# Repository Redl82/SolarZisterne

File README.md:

# SolarZisterne

Es handelt sich bei diesem Projekt um einen Füllstandsmesser für eine Außen-Zisterne.
Der Füllstandsmesser wir über einen ESP8266 mit dem Netzwerkverbunden und agiert als eigenständiger Web-Server.
Die Stromversorgung wird über Solarzellen gewährleistet.
Das Projekt besitz die folgenden Sensoren:
- Ultraschall Sensor für Füllstand
- Temperatur/Luftfeuchte/Luftdruck Sensor außen
- Temperatur/Luftdruck Sensor innen
- Spannung/Strom Sensor Produktion Solarzellen
- Spannung/Strom Sensor Verbrauch Elektronik

Die Lade Schaltung kann die follgenden Zustände annehmen:
            GPIO2   GPIO1   GPIO0
     Wert   STAT1   STAT2   PG      Status
     7      1       1       1       Input Power Not OK / Shutdown
     6      1       1       0       Input Power OK / No Battery Present
     4      1       0       0       Input Power OK / Charge Complete - Standby
     3      0       1       1       Input Power Not OK / Low Battery Output
     2      0       1       0       Input Power OK / Chargin Batter in Constant Current/Voltage or Preconding Mode
     0      0       0       0       Input Power OK / Temperature Fault / Temperatur Fault

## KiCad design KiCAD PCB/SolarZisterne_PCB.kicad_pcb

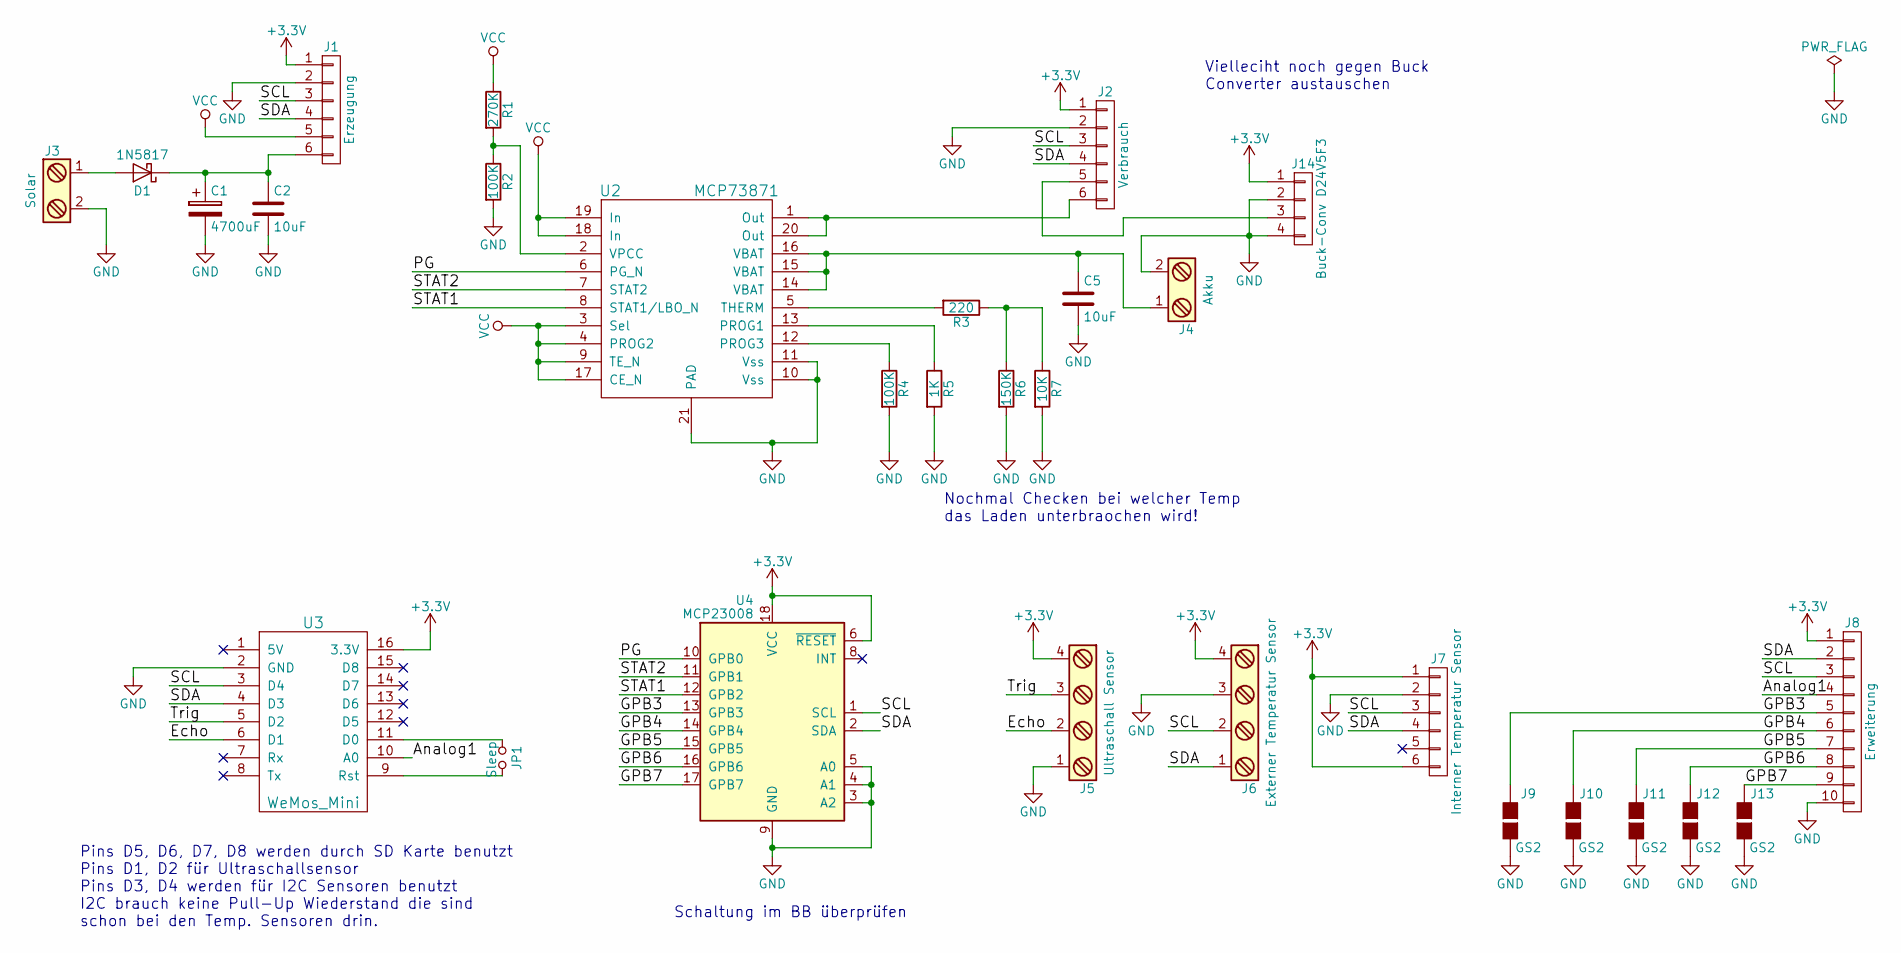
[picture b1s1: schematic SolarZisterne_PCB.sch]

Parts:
C1: 4700uF; CP_Radial_D16.0mm_P7.50mm
C2, C5: 10uF; C_Disc_D5.0mm_W2.5mm_P2.50mm
D1: 1N5817; D_DO-41_SOD81_P10.16mm_Horizontal
J1: Erzeugung; Pin_Header_Straight_1x06_Pitch2.54mm
J2: Verbrauch; Pin_Header_Straight_1x06_Pitch2.54mm
J3: Solar; TerminalBlock_Pheonix_PT-3.5mm_2pol
J4: Akku; TerminalBlock_Pheonix_PT-3.5mm_2pol
J5: Ultraschall Sensor; TerminalBlock_Pheonix_PT-3.5mm_4pol
J6: Externer Temperatur Sensor; TerminalBlock_Pheonix_PT-3.5mm_4pol
J7: Interner Temperatur Sensor; Pin_Header_Straight_1x06_Pitch2.54mm
J8: Erweiterung; Pin_Header_Straight_1x10_Pitch2.54mm
J9, J10, J11, J12, J13: GS2
J14: Buck-Conv D24V5F3; Pin_Header_Straight_1x04_Pitch2.54mm
JP1: Sleep; Pin_Header_Straight_1x02_Pitch2.54mm
R1: 270K; R_Axial_DIN0207_L6.3mm_D2.5mm_P10.16mm_Horizontal
R2, R4: 100K; R_Axial_DIN0207_L6.3mm_D2.5mm_P10.16mm_Horizontal
R3: 220; R_Axial_DIN0207_L6.3mm_D2.5mm_P10.16mm_Horizontal
R5: 1K; R_Axial_DIN0207_L6.3mm_D2.5mm_P10.16mm_Horizontal
R6: 150K; R_Axial_DIN0207_L6.3mm_D2.5mm_P10.16mm_Horizontal
R7: 10K; R_Axial_DIN0207_L6.3mm_D2.5mm_P10.16mm_Horizontal
U2: MCP73871; QFN-20-1EP_4x4mm_Pitch0.5mm
U3: WeMos_Mini; D1_mini_board
U4: MCP23008; DIP-18_W7.62mm_LongPads

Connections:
+3V3: J1.1, J2.1, J5.4, J6.4, J7.1, J7.6, J8.1, J14.1, U3.16 (3.3V), U4.6 (~RESET), U4.18 (VCC)
/Analog1: J8.4, U3.10 (A0)
/Echo: J5.2, U3.6 (D1)
/GPB3: J8.5, J9.1 (G1), U4.13 (GPB3)
/GPB4: J8.6, J10.1 (G1), U4.14 (GPB4)
/GPB5: J8.7, J11.1 (G1), U4.15 (GPB5)
/GPB6: J8.8, J12.1 (G1), U4.16 (GPB6)
/GPB7: J8.9, J13.1 (G1), U4.17 (GPB7)
/PG: U2.6 (PG_N), U4.10 (GPB0)
/SCL: J1.3, J2.3, J6.2, J7.3, J8.3, U3.3 (D4), U4.1 (SCL)
/SDA: J1.4, J2.4, J6.1, J7.4, J8.2, U3.4 (D3), U4.2 (SDA)
/STAT1: U2.8 (STAT1/LBO_N), U4.12 (GPB2)
/STAT2: U2.7 (STAT2), U4.11 (GPB1)
/Trig: J5.3, U3.5 (D2)
GND: C1.2, C2.2, C5.2, J1.2, J2.2, J3.2, J4.2, J5.1, J6.3, J7.2, J8.10, J9.2 (G2), J10.2 (G2), J11.2 (G2), J12.2 (G2), J13.2 (G2), J14.2, J14.4, R2.2, R4.2, R5.2, R6.2, R7.2, U2.10 (Vss), U2.11 (Vss), U2.21 (PAD), U3.2 (GND), U4.3 (A2), U4.4 (A1), U4.5 (A0), U4.9 (GND)
unnamed: C1.1, C2.1, D1.1 (K), J1.6
unnamed: C5.1, J4.1, U2.14 (VBAT), U2.15 (VBAT), U2.16 (VBAT)
unnamed: D1.2 (A), J3.1
unnamed: J2.6, U2.1 (Out), U2.20 (Out)
unnamed: J2.5, J14.3
unnamed: JP1.1, U3.11 (D0)
unnamed: JP1.2, U3.9 (Rst)
unnamed: R1.2, R2.1, U2.2 (VPCC)
unnamed: R3.1, R6.1, R7.1
unnamed: R3.2, U2.5 (THERM)
unnamed: R4.1, U2.12 (PROG3)
unnamed: R5.1, U2.13 (PROG1)
VCC: J1.5, R1.1, U2.3 (Sel), U2.4 (PROG2), U2.9 (TE_N), U2.17 (CE_N), U2.18 (In), U2.19 (In)

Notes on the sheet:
Pins D5, D6, D7, D8 werden durch SD Karte benutzt Pins D1, D2 für Ultraschallsensor Pins D3, D4 werden für I2C Sensoren benutzt I2C brauch keine Pull-Up Wiederstand die sind schon bei den Temp. Sensoren drin.
Nochmal Checken bei welcher Temp das Laden unterbraochen wird!
Schaltung im BB überprüfen
Vielleciht noch gegen Buck Converter austauschen

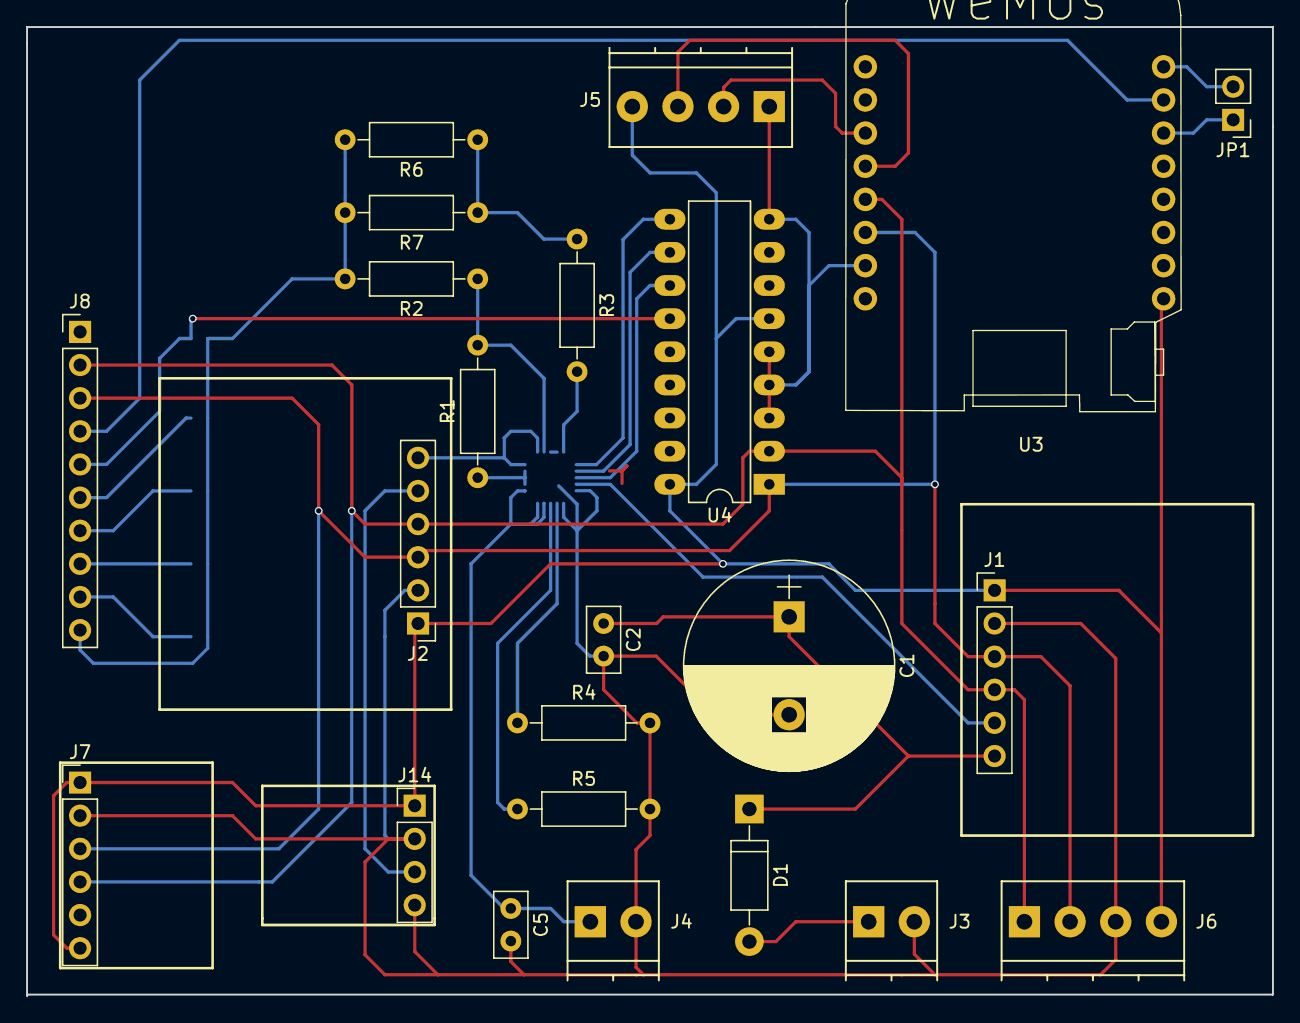
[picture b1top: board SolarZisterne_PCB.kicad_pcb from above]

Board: 2 copper layers, 95.5 x 74.3 mm, 29 parts (0 on the bottom side), 28 nets.

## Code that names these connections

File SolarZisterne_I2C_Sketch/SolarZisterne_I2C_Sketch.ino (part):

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// Ultraschall Sensor HC-SR04 Pin definition
//////////////////////////////
#define TRIGGER D4
#define ECHO    D3

// set up variables using the SD utility library functions:
Sd2Card card;
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  Serial.println("GPIO Erweiterung auf 0x20 eingerichtet!");
  
  mcp.pinMode(0, INPUT);      // definiert Pin 0 als Input --> PG
  mcp.pinMode(1, INPUT);      // definiert Pin 1 als Input --> STAT2
  mcp.pinMode(2, INPUT);      // definiert Pin 2 als Input --> STAT1
  mcp.pullUp(0, HIGH);        // turn on a 100K pullup internally
  mcp.pullUp(1, HIGH);        // turn on a 100K pullup internally
  mcp.pullUp(2, HIGH);        // turn on a 100K pullup internally

  Serial.println("GPIO0 --> PG");
  Serial.println("GPIO1 --> STAT1");
  Serial.println("GPIO2 --> STAT2");

  Serial.println("Pull-Up Wiederstände wurden eingeschaltet");
  
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  
  //Definition der Pins für Ultraschall Sensor
  pinMode(TRIGGER, OUTPUT);
  pinMode(ECHO, INPUT);
  Serial.println("########################################################################################################");
  Serial.println("");
  Serial.println("Ultraschall Sensor wurde wie folgt eingerichte:");
  Serial.println("Ultraschall Sensor wird eingerichte:");
  Serial.print("Triger auf Pin ");
  Serial.println(TRIGGER);
  Serial.print("Echo auf Pin ");
  Serial.println(ECHO);
  Serial.println("");
  Serial.println("Ultraschall Sensor wurde wie folgt eingerichte:");
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
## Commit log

2017-06-25 Initial Version
2017-06-25 DHT Sensoren funktionieren
2017-06-25 ACS712 strommessung implementiert
    Sehr ungenau bei 0A Messung zeigt an das 50-100 mA fließen
2017-06-26 Konzept auf I2C
    Alle Temp und Strom Senoren werden über I2C angesteuert Digitale I/O werden auch über I2C erweiter. Kein AT MEGA mehr.
2017-06-28 Erster Entwurf des kompletten Schaltplans
2017-06-30 Thermal Sensoren eingefügt
2017-07-02 PCB angefangen
2017-07-02 weiter gearbeite
2017-07-02 Aufgeräumt und am Programm gearbeitet
2017-07-03 GPIO Expander eingebunden
2017-07-09 Sicherung bevor die Messung mit den DHT22 Sensoren entfernt wird
2017-07-15 Sketche Entfernt
2017-07-15 Before Änderung Ultraschall
2017-07-23 PCB Update
2017-07-26 fast aller Leiterbahnen
